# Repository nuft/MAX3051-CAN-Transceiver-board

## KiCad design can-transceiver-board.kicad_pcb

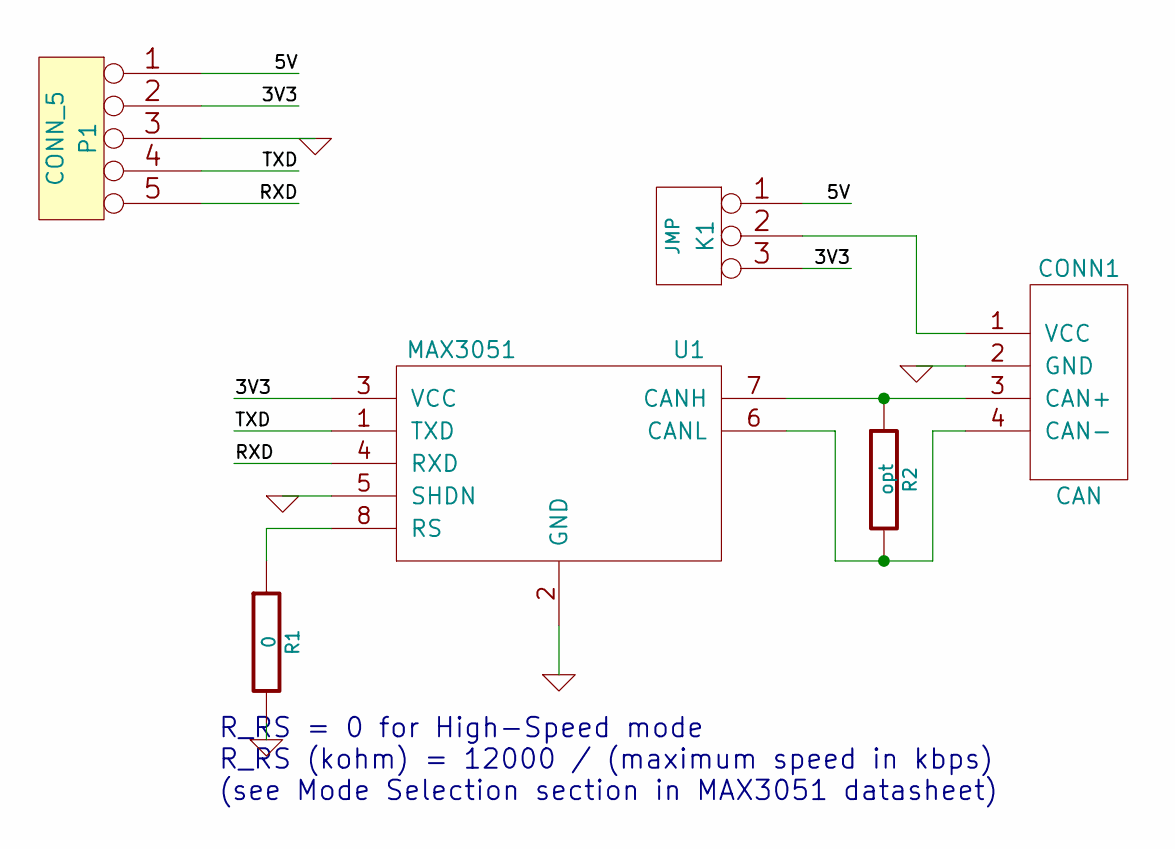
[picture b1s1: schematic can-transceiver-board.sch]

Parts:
CONN1: CAN; MODULE
K1: JMP
P1: CONN_5
R1: 0
R2: opt
U1: MAX3051; MODULE

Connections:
/3V3: K1.3, P1.2, U1.3 (VCC)
/5V: K1.1, P1.1
/RXD: P1.5, U1.4 (RXD)
/TXD: P1.4, U1.1 (TXD)
GND: CONN1.2 (GND), CONN1.MECH (GND), P1.3, R1.2, U1.2 (GND), U1.5 (SHDN)
unnamed: CONN1.1 (VCC), K1.2 (PM)
unnamed: CONN1.3 (CAN+), R2.1, U1.7 (CANH)
unnamed: CONN1.4 (CAN-), R2.2, U1.6 (CANL)
unnamed: R1.1, U1.8 (RS)

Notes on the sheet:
R_RS = 0 for High-Speed mode R_RS (kohm) = 12000 / (maximum speed in kbps) (see Mode Selection section in MAX3051 datasheet)

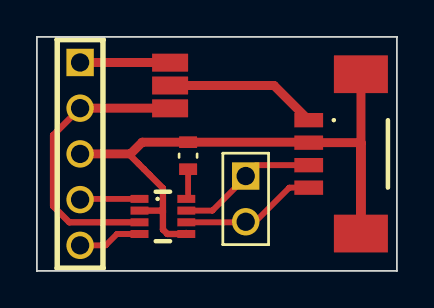
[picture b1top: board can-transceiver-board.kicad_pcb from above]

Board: 2 copper layers, 20.0 x 13.0 mm, 6 parts (0 on the bottom side), 9 nets.

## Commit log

2014-10-15 Add project and schematic files
2014-10-15 Add kicad libarary
2014-10-21 first schematic and pcb layout version.
2014-11-26 Improved GND routing, added CAN terminal resistor pin.
2014-11-26 Increased solder jumper pad width.
2014-12-07 Add text to silkscreen, increased power tracks.
2014-12-07 Gerber files for manufacturing.
